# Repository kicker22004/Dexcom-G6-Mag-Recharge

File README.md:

# Dexcom-G6-Mag-Recharge-
### Rechargeable Dexcom board and steps

# WARNING!!!!.
### This is a DIY project that you will attach a LIPO battery to your body, This comes with risks and as such if you decide to build one for yourself you are doing so at your own risk and I will not be held responsible for any and all injuries or damages to you or your Transmitters.

Ok with that out of the way I have several test users that have had great success using their devices and figured it's time to share.
There are a lot of teardown video's out there for removing the battery from your Dexcom device so please look around.
There are a few differences in my design in the fact that we will be opening up the rear of the device and creating space for the battery.
This will require patients, skill, and a bit of luck.

## Parts Required:
- PCB (Link)
- 3.7V 30mAh lipo (Part Number 301012)
- MCP73831T-2 SOT23
- 2x - 10uf 0402
- Green LED 0402
- Red LED 0402
- 2x - 470k Resistor 0402
- 10k Resistor 0402
- BAT54SLT1G SOT-23
- Magnetic Connector (8MM)

## Resources:
I will update this as I have time to include where you can get cables and parts, But for now the parts can be sourced on ebay,digikey,mouser and i'm sure other locations. I'll also attempt to build a wiki for this project but that will come with intrest and time.

## Helpful Tools:
- Reflow station or Reflow Oven
- My reflow station was cheap (858D+ 220V Hot Air Soldering ReWork Station)

### A Stencil for the pcb!!, not required but super useful!
I ordered mine with the pcb from Jlcpcb.com

- A Digital Microscope. Mine was also cheap (Andonstar ADSM302)

- Soldering Iron for the wires, Magnetic connector and attaching the battery. Mine is a simple TS100 iron.

## Donation:
Never required or requested but always appreciated :)

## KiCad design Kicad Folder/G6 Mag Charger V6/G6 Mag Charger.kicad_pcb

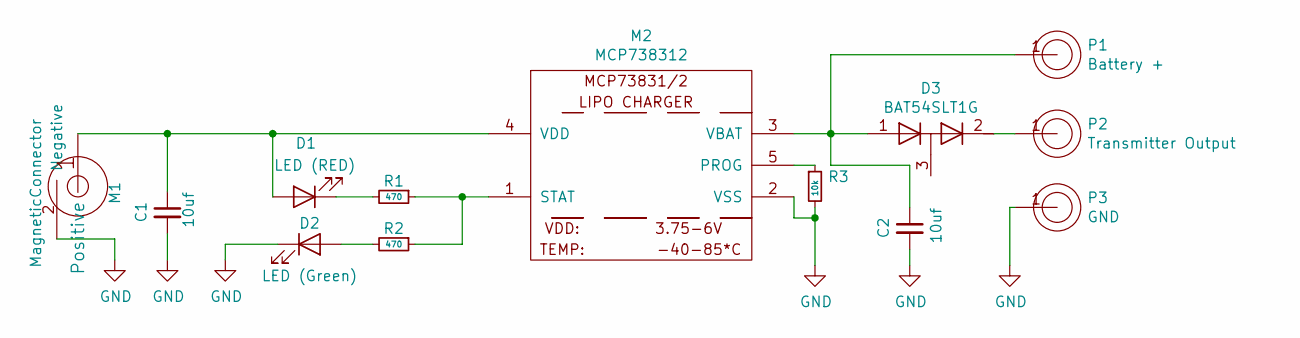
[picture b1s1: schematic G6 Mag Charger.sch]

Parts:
C1, C2: 10uf; C_0402
D1: LED (RED); LED_0402
D2: LED (Green); LED_0402
D3: BAT54SLT1G; SOT-23
M1: MagneticConnector; Magnetic Port
M2: MCP738312; SOT-23-5
P1: Battery +; G6 Pad
P2: Transmitter Output; G6 Pad
P3: GND; G6 Pad
R1, R2: 470; R_0402
R3: 10k; R_0402

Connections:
GND: C1.2, C2.2, D2.1 (K), M1.2 (Negative), M2.2 (VSS), P3.1, R3.2
unnamed: C1.1, D1.2 (A), M1.1 (Positive), M2.4 (VDD)
unnamed: C2.1, D3.1 (A), M2.3 (VBAT), P1.1
unnamed: D1.1 (K), R1.2
unnamed: D2.2 (A), R2.2
unnamed: D3.2 (K), P2.1
unnamed: M2.1 (STAT), R1.1, R2.1
unnamed: M2.5 (PROG), R3.1

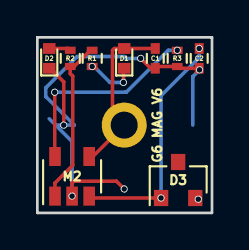
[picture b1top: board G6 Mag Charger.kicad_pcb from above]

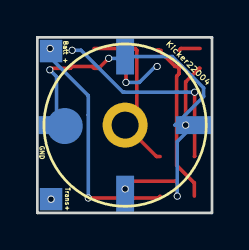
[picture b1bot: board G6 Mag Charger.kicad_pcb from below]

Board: 2 copper layers, 9.7 x 9.8 mm, 13 parts (4 on the bottom side), 8 nets.

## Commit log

2020-10-19 Fixed short on the Red Led
